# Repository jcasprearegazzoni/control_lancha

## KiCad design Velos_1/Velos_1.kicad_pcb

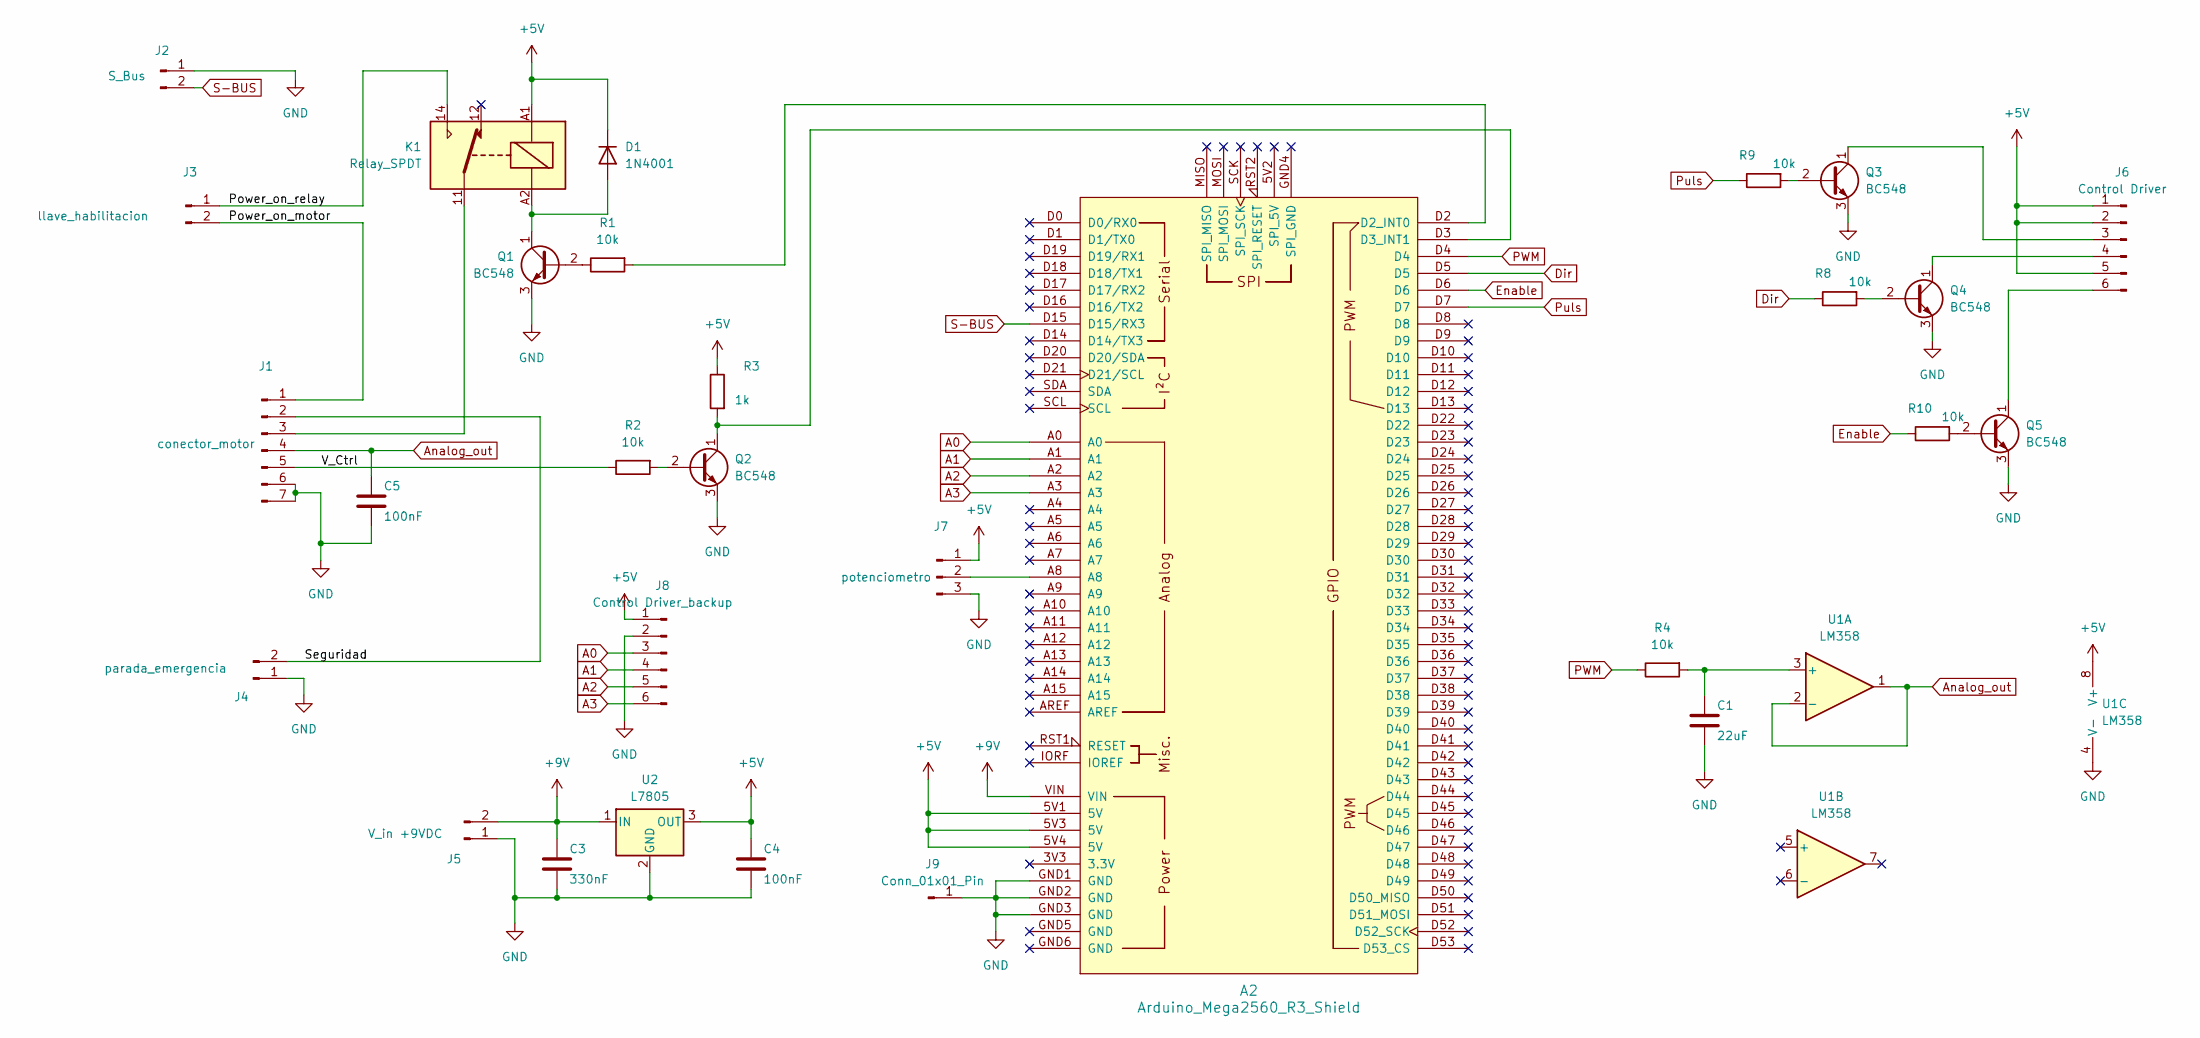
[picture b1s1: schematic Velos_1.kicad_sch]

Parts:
A2: Arduino_Mega2560_R3_Shield; Arduino_Mega2560_Shield
C1: 22uF; CP_Radial_D6.3mm_P2.50mm
C3: 330nF; C_Disc_D5.0mm_W2.5mm_P5.00mm
C4, C5: 100nF; C_Disc_D5.0mm_W2.5mm_P5.00mm
D1: 1N4001; D_DO-41_SOD81_P10.16mm_Horizontal
J1: conector_motor; TerminalBlock_Phoenix_MKDS-1,5-7_1x07_P5.00mm_Horizontal
J2: S_Bus; PinHeader_1x02_P2.54mm_Vertical
J3: llave_habilitacion; TerminalBlock_Phoenix_MKDS-1,5-2_1x02_P5.00mm_Horizontal
J4: parada_emergencia; TerminalBlock_Phoenix_MKDS-1,5-2_1x02_P5.00mm_Horizontal
J5: V_in +9VDC; TerminalBlock_Phoenix_MKDS-1,5-2_1x02_P5.00mm_Horizontal
J6: Control Driver; TerminalBlock_Phoenix_MKDS-1,5-6_1x06_P5.00mm_Horizontal
J7: potenciometro; PinHeader_1x03_P2.54mm_Vertical
J8: Control Driver_backup; PinHeader_1x06_P2.54mm_Vertical
J9: Conn_01x01_Pin; PinHeader_1x01_P2.54mm_Vertical
K1: Relay_SPDT; Relay_SPDT_Hongfa_JQC-3FF_0XX-1Z
Q1, Q2, Q3, Q4, Q5: BC548; TO-92_Inline
R1, R2, R4, R8, R9, R10: 10k; R_Axial_DIN0204_L3.6mm_D1.6mm_P7.62mm_Horizontal
R3: 1k; R_Axial_DIN0204_L3.6mm_D1.6mm_P7.62mm_Horizontal
U1: LM358; DIP-8_W7.62mm_Socket_LongPads
U2: L7805; TO-220-3_Vertical

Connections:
+5V: A2.5V1 (5V), A2.5V3 (5V), A2.5V4 (5V), C4.1, D1.1 (K), J6.1, J6.2, J6.5, J7.1, J8.1, K1.A1, R3.1, U1.8 (V+), U2.3 (OUT)
+9V: A2.VIN, C3.1, J5.2, U2.1 (IN)
/Power_on_motor: J1.1, J3.2
/Power_on_relay: J3.1, K1.14
/Seguridad: J1.2, J4.2
/V_Ctrl: J1.5, R2.1
A0: A2.A0, J8.3
A1: A2.A1, J8.4
A2: A2.A2, J8.5
A3: A2.A3, J8.6
Analog_out: C5.1, J1.4, U1.1, U1.2 (-)
Dir: A2.D5, R8.1
Enable: A2.D6, R10.1
GND: A2.GND1 (GND), A2.GND2 (GND), A2.GND3 (GND), C1.2, C3.2, C4.2, C5.2, J1.6, J1.7, J2.1, J4.1, J5.1, J7.3, J8.2, J9.1 (Pin_1_1), Q1.3 (E), Q2.3 (E), Q3.3 (E), Q4.3 (E), Q5.3 (E), U1.4 (V-), U2.2 (GND)
unnamed: A2.D2 (D2_INT0), R1.2
unnamed: A2.D3 (D3_INT1), Q2.1 (C), R3.2
unnamed: D1.2 (A), K1.A2, Q1.1 (C)
unnamed: J1.3, K1.11
unnamed: J6.3, Q3.1 (C)
unnamed: J6.4, Q4.1 (C)
unnamed: J6.6, Q5.1 (C)
unnamed: A2.A8, J7.2
unnamed: Q1.2 (B), R1.1
unnamed: Q2.2 (B), R2.2
unnamed: Q3.2 (B), R9.2
unnamed: Q4.2 (B), R8.2
unnamed: Q5.2 (B), R10.2
unnamed: C1.1, R4.2, U1.3 (+)
PWM: A2.D4, R4.1
Puls: A2.D7, R9.1
S-BUS: A2.D15 (D15/RX3), J2.2

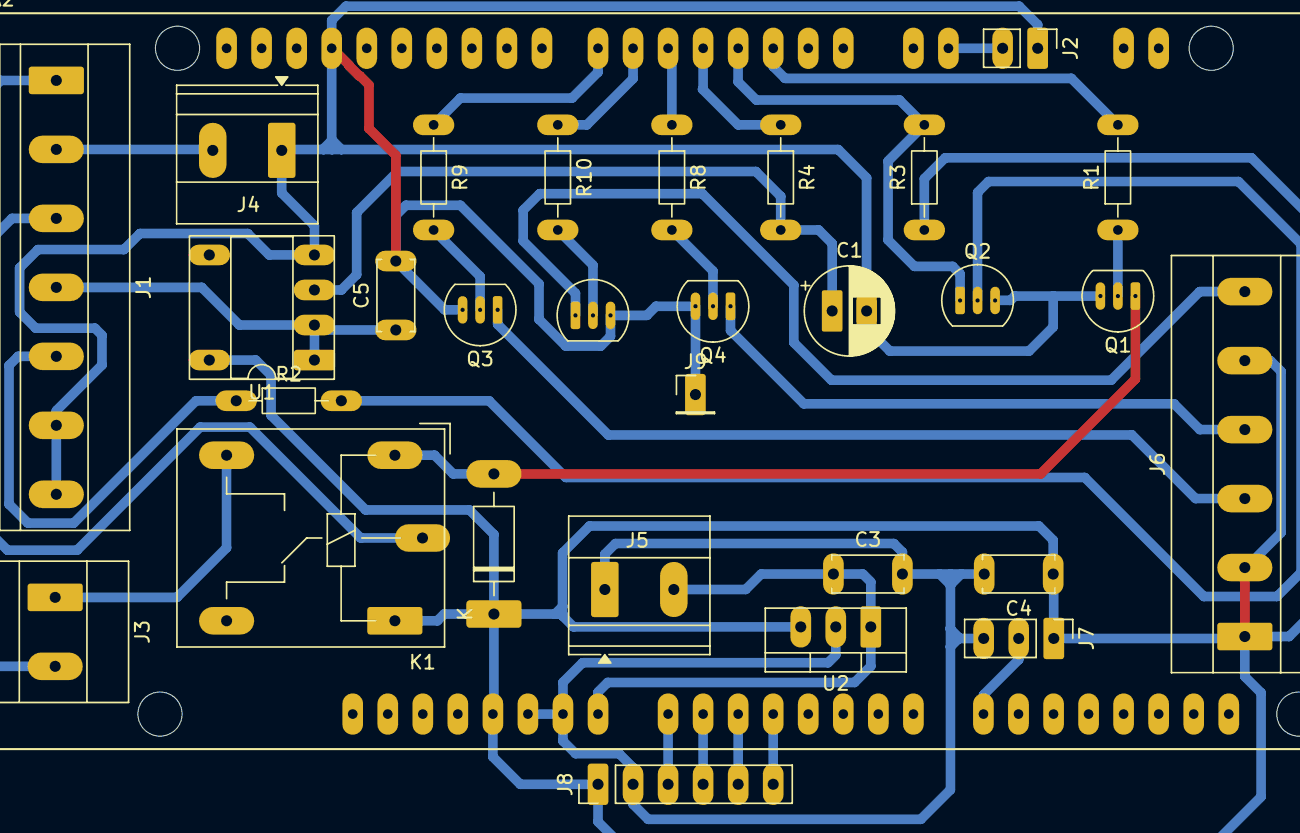
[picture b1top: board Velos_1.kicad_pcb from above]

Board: 2 copper layers, 30 parts (0 on the bottom side), 31 nets.
